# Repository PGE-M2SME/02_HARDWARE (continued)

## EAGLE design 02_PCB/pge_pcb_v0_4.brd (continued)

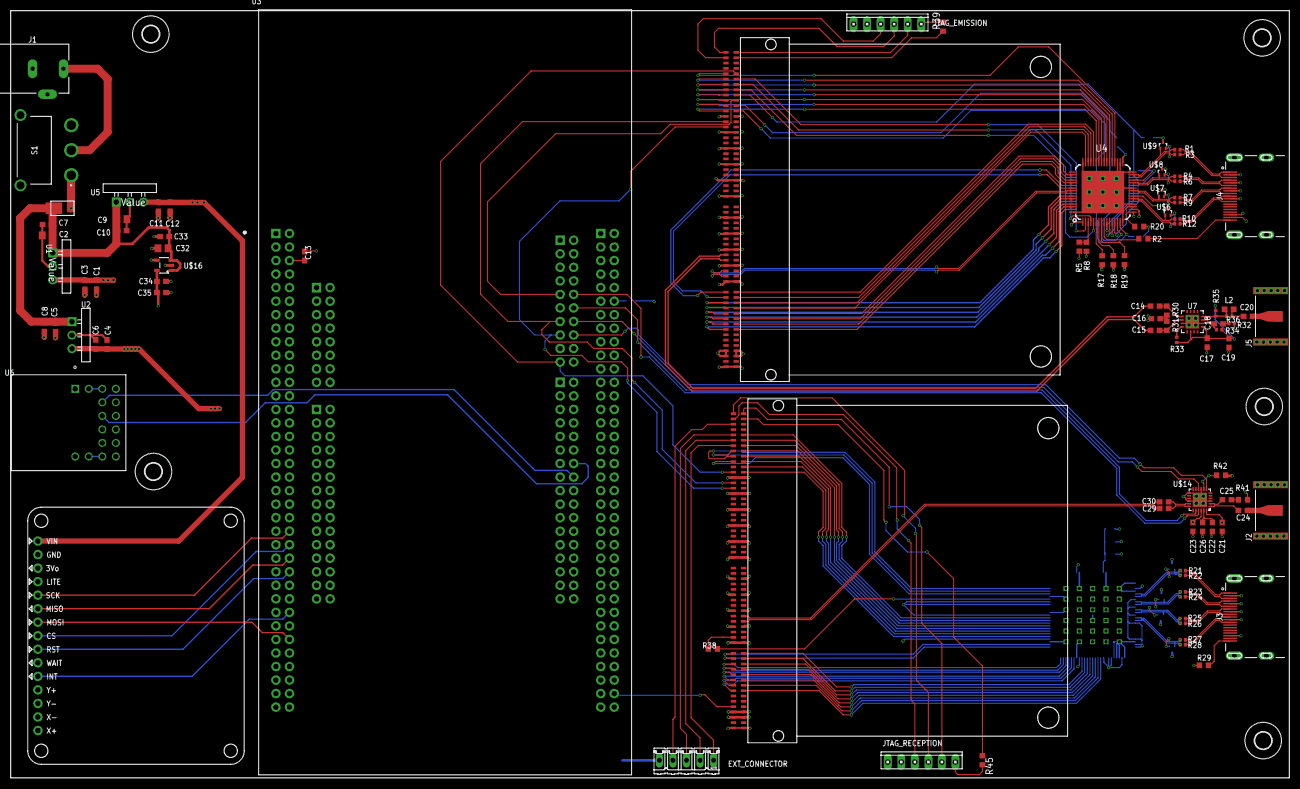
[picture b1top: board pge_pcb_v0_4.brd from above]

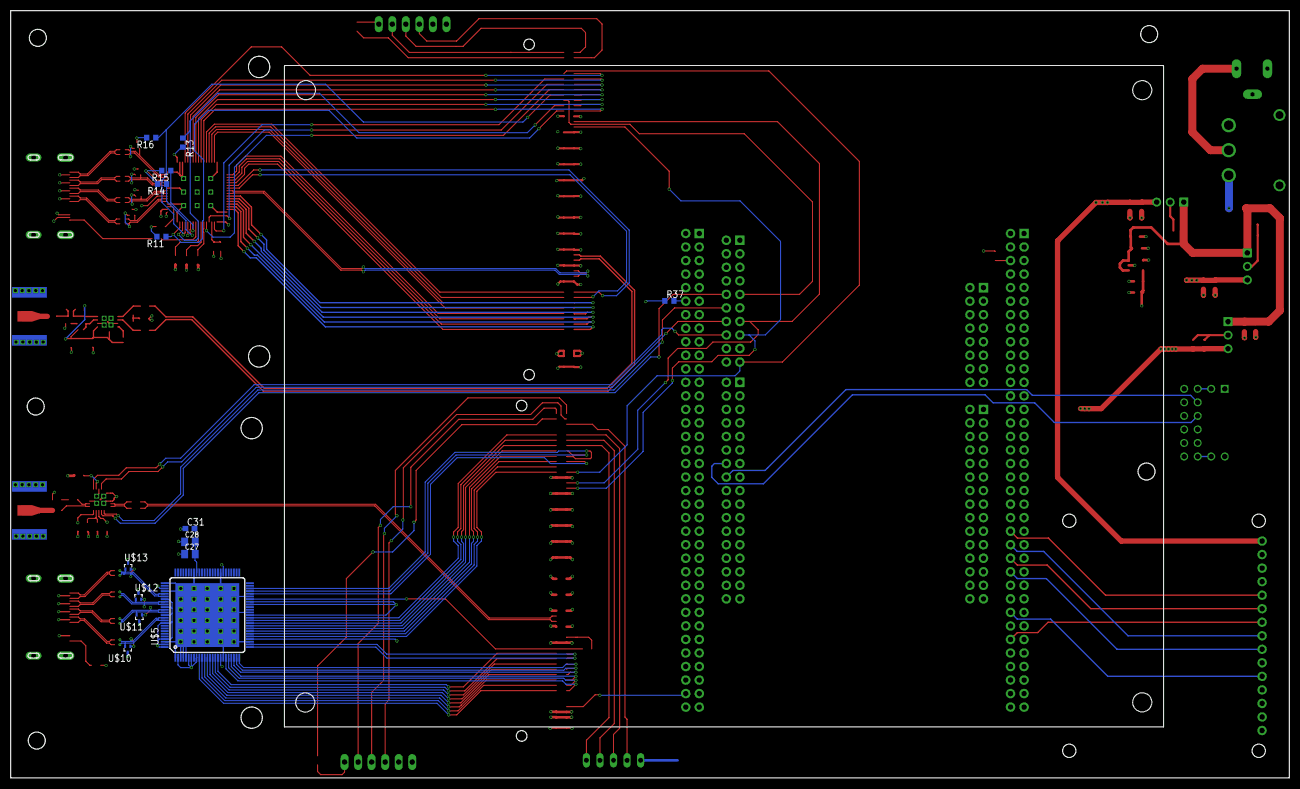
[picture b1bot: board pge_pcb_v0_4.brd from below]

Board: 6 copper layers, 240.0 x 144.0 mm, 115 parts (15 on the bottom side), 167 nets.

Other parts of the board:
H1, H2, H3, H7: MOUNT-HOLE3.2; 3,2

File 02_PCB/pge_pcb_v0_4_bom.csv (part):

"Qty";"Value";"Device";"Package";"Parts";"Description";"AMBIENT_TEMPERATURE_RANGE_HIGH";"AMBIENT_TEMPERATURE_RANGE_LOW";"ARROW_PART_NUMBER";"ARROW_PRICE-STOCK";"AUTOMOTIVE";"AVAILABILITY";"CENTROID_NOT_SPECIFIED";"DATASHEET";"DATASHEET-URL";"DESCRIPTION";"DEVICE_CLASS_L1";"DEVICE_CLASS_L2";"DEVICE_CLASS_L3";"DIGIKEY_DESCRIPTION";"DIGIKEY_PART_NUMBER";"FOOTPRINT_PARAMETERS_1";"FOOTPRINT_PARAMETERS_2";"FOOTPRINT_PARAMETERS_3";"FOOTPRINT_VARIANT_NAME_0";"FOOTPRINT_VARIANT_NAME_1";"FOOTPRINT_VARIANT_NAME_2";"FOOTPRINT_VARIANT_NAME_3";"GERDER";"HEIGHT";"INTERFACE";"IPC_LAND_PATTERN_NAME";"IR";"LEAD_FREE";"MANUFACTURER";"MANUFACTURER_NAME";"MANUFACTURER_PART_NUMBER";"MAXIMUM_PACKAGE_HEIGHT";"MAX_JUNCTION_TEMP";"MAX_SUPPLY_VOLTAGE";"MF";"MFG_PACKAGE_IDENT";"MFG_PACKAGE_IDENT_COMPONENT_ID";"MFG_PACKAGE_IDENT_DATE";"MFG_PACKAGE_IDENT_REV";"MIN_SUPPLY_VOLTAGE";"MOUNT";"MOUSER_DESCRIPTION";"MOUSER_PART_NUMBER";"MOUSER_PRICE-STOCK";"MP";"MPN";"NOMINAL_SUPPLY_CURRENT";"OC_FARNELL";"OC_NEWARK";"PACKAGE";"PART-NUMBER";"PARTNUMBER";"PARTREV";"PINS";"POPULARITY";"PREFIX";"PRICE";"PURCHASE-URL";"RATED-CURRENT";"REFDES";"ROHS";"SPICEPREFIX";"STANDARD";"TEMPERATURE_RANGE_HIGH";"TEMPERATURE_RANGE_LOW";"TYPE";"VALUE";"VERIFICATION_VERSION";"WORKING-VOLTAGE";
"2";"";"685119134923";"685119134923";"J3, J4";"WR-COM HDMI SMT Horizontal";"";"";"";"";"";"";"";"";"https://www.we-online.com/catalog/datasheet/685119134923.pdf";"";"";"";"";"";"";"";"";"";"";"";"";"";"Receptacle";"";"";"";"";"";"";"";"";"";"";"";"";"";"";"";"";"";"SMT";"";"";"";"";"";"";"";"";"";"685119134923";"";"";" 19 ";"";"";"";"";"0.5A";"";"";"";"";"";"";"Horizontal";"";"";"40VDC";
"1";"";"694106301002";"694106301002";"J1";"WR-DC DC Power Jack Right Angled (6.4)";"";"";"";"";"";"";"";"";"https://katalog.we-online.com/em/datasheet/694106301002.pdf";"";"";"";"";"";"";"";"";"";"";"";"";"";"";"";"";"";"5A";"";"";"";"";"";"";"";"";"";"";"";"";"";"THT";"";"";"";"";"";"";"";"";"";" 694106301002 ";"";"";"";"";"";"";"";"";"";"";"";"";"";"";"Right Angled";"";"";"30V(AC)";
"1";"";"M05";"05P";"EXT_CONNECTOR";"AMP QUICK CONNECTOR";"";"";"";"";"";"";"";"";"";"";"";"";"";"";"";"";"";"";"";"";"";"";"";"";"";"";"";"";"";"";"";"";"";"";"";"";"";"";"";"";"";"";"";"";"";"";"";"unknown";"unknown";"";"";"";"";"";"16";"";"";"";"";"";"";"";"";"";"";"";"";"";"";
"2";"";"MTA06-100";"10X06MTA";"JTAG_EMISSION, JTAG_RECEPTION";"AMP connector";"";"";"";"";"";"";"";"";"";"";"";"";"";"";"";"";"";"";"";"";"";"";"";"";"";"";"";"";"";"";"";"";"";"";"";"";"";"";"";"";"";"";"";"";"";"";"";"";"";"";"";"";"";"";"0";"";"";"";"";"";"";"";"";"";"";"";"";"";"";
"3";"0R";"R-EU_R0603";"R0603";"R17, R18, R19";"RESISTOR, European symbol";"";"";"";"";"";"";"";"";"";"";"";"";"";"";"";"";"";"";"";"";"";"";"";"";"";"";"";"";"";"";"";"";"";"";"";"";"";"";"";"";"";"";"";"";"";"";"";"";"";"";"";"";"";"";"70";"";"";"";"";"";"";"R";"";"";"";"";"";"";"";
"1";"1.5k";"R-EU_R0603";"R0603";"R37";"RESISTOR, European symbol";"";"";"";"";"";"";"";"";"";"";"";"";"";"";"";"";"";"";"";"";"";"";"";"";"";"";"";"";"";"";"";"";"";"";"";"";"";"";"";"";"";"";"";"";"";"";"";"";"";"";"";"";"";"";"70";"";"";"";"";"";"";"R";"";"";"";"";"";"";"";
"16";"100nF";"C-EUC0603";"C0603";"C1, C4, C7, C8, C10, C11, C13, C16, C17, C19, C21, C22, C23, C31, C33, C35";"CAPACITOR, European symbol";"";"";"";"";"";"";"";"";"";"";"";"";"";"";"";"";"";"";"";"";"";"";"";"";"";"";"";"";"";"";"";"";"";"";"";"";"";"";"";"";"";"";"";"";"";"";"";"";"";"";"";"";"";"";"73";"";"";"";"";"";"";"C";"";"";"";"";"";"";"";
"5";"10uF";"C-EUC0603";"C0603";"C3, C5, C6, C12, C34";"CAPACITOR, European symbol";"";"";"";"";"";"";"";"";"";"";"";"";"";"";"";"";"";"";"";"";"";"";"";"";"";"";"";"";"";"";"";"";"";"";"";"";"";"";"";"";"";"";"";"";"";"";"";"";"";"";"";"";"";"";"73";"";"";"";"";"";"";"C";"";"";"";"";"";"";"";
"3";"10uF";"C-EUC0805";"C0805";"C2, C9, C32";"CAPACITOR, European symbol";"";"";"";"";"";"";"";"";"";"";"";"";"";"";"";"";"";"";"";"";"";"";"";"";"";"";"";"";"";"";"";"";"";"";"";"";"";"";"";"";"";"";"";"";"";"";"";"";"";"";"";"";"";"";"88";"";"";"";"";"";"";"C";"";"";"";"";"";"";"";
"3";"1k";"R-EU_R0603";"R0603";"R2, R29, R42";"RESISTOR, European symbol";"";"";"";"";"";"";"";"";"";"";"";"";"";"";"";"";"";"";"";"";"";"";"";"";"";"";"";"";"";"";"";"";"";"";"";"";"";"";"";"";"";"";"";"";"";"";"";"";"";"";"";"";"";"";"70";"";"";"";"";"";"";"R";"";"";"";"";"";"";"";
"3";"1uF";"C-EUC0603";"C0603";"C14, C15, C26";"CAPACITOR, European symbol";"";"";"";"";"";"";"";"";"";"";"";"";"";"";"";"";"";"";"";"";"";"";"";"";"";"";"";"";"";"";"";"";"";"";"";"";"";"";"";"";"";"";"";"";"";"";"";"";"";"";"";"";"";"";"73";"";"";"";"";"";"";"C";"";"";"";"";"";"";"";
"1";"2.43K";"R-EU_R0603";"R0603";"R5";"RESISTOR, European symbol";"";"";"";"";"";"";"";"";"";"";"";"";"";"";"";"";"";"";"";"";"";"";"";"";"";"";"";"";"";"";"";"";"";"";"";"";"";"";"";"";"";"";"";"";"";"";"";"";"";"";"";"";"";"";"70";"";"";"";"";"";"";"R";"";"";"";"";"";"";"";
"1";"22R";"R-EU_R0603";"R0603";"R38";"RESISTOR, European symbol";"";"";"";"";"";"";"";"";"";"";"";"";"";"";"";"";"";"";"";"";"";"";"";"";"";"";"";"";"";"";"";"";"";"";"";"";"";"";"";"";"";"";"";"";"";"";"";"";"";"";"";"";"";"";"70";"";"";"";"";"";"";"R";"";"";"";"";"";"";"";
"2";"22uF";"C-EUC0805K";"C0805K";"C27, C28";"CAPACITOR, European symbol";"";"";"";"";"";"";"";"";"";"";"";"";"";"";"";"";"";"";"";"";"";"";"";"";"";"";"";"";"";"";"";"";"";"";"";"";"";"";"";"";"";"";"";"";"";"";"";"";"";"";"";"";"";"";"52";"";"";"";"";"";"";"C";"";"";"";"";"";"";"";
"16";"28R";"R-EU_R0402";"R0402";"R1, R3, R4, R6, R7, R9, R10, R12, R21, R22, R23, R24, R25, R26, R27, R28";"RESISTOR, European symbol";"";"";"";"";"";"";"";"";"";"";"";"";"";"";"";"";"";"";"";"";"";"";"";"";"";"";"";"";"";"";"";"";"";"";"";"";"";"";"";"";"";"";"";"";"";"";"";"";"";"";"";"";"";"";"0";"";"";"";"";"";"";"R";"";"";"";"";"";"";"";
"6";"4.7uF";"C-EUC0603";"C0603";"C18, C20, C24, C25, C29, C30";"CAPACITOR, European symbol";"";"";"";"";"";"";"";"";"";"";"";"";"";"";"";"";"";"";"";"";"";"";"";"";"";"";"";"";"";"";"";"";"";"";"";"";"";"";"";"";"";"";"";"";"";"";"";"";"";"";"";"";"";"";"73";"";"";"";"";"";"";"C";"";"";"";"";"";"";"";
"1";"499 R";"R-EU_R0603";"R0603";"R20";"RESISTOR, European symbol";"";"";"";"";"";"";"";"";"";"";"";"";"";"";"";"";"";"";"";"";"";"";"";"";"";"";"";"";"";"";"";"";"";"";"";"";"";"";"";"";"";"";"";"";"";"";"";"";"";"";"";"";"";"";"70";"";"";"";"";"";"";"R";"";"";"";"";"";"";"";
"2";"50R";"R-EU_R0603";"R0603";"R30, R31";"RESISTOR, European symbol";"";"";"";"";"";"";"";"";"";"";"";"";"";"";"";"";"";"";"";"";"";"";"";"";"";"";"";"";"";"";"";"";"";"";"";"";"";"";"";"";"";"";"";"";"";"";"";"";"";"";"";"";"";"";"70";"";"";"";"";"";"";"R";"";"";"";"";"";"";"";
"5";"5k";"R-EU_R0603";"R0603";"R11, R13, R14, R15, R16";"RESISTOR, European symbol";"";"";"";"";"";"";"";"";"";"";"";"";"";"";"";"";"";"";"";"";"";"";"";"";"";"";"";"";"";"";"";"";"";"";"";"";"";"";"";"";"";"";"";"";"";"";"";"";"";"";"";"";"";"";"70";"";"";"";"";"";"";"R";"";"";"";"";"";"";"";
"1";"6.8nH";"L0603";"L0603";"L2";"";"";"";"";"";"";"";"";"";"";"";"";"";"";"";"";"";"";"";"";"";"";"";"";"";"";"";"";"";"";"";"";"";"";"";"";"";"";"";"";"";"";"";"";"";"";"";"";"";"";"";"";"";"";"";"";"";"";"";"";"";"";"";"";"";"";"";"";"";"";
"1";"750R";"R-EU_R0402";"R0402";"R33";"RESISTOR, European symbol";"";"";"";"";"";"";"";"";"";"";"";"";"";"";"";"";"";"";"";"";"";"";"";"";"";"";"";"";"";"";"";"";"";"";"";"";"";"";"";"";"";"";"";"";"";"";"";"";"";"";"";"";"";"";"0";"";"";"";"";"";"";"R";"";"";"";"";"";"";"";
"4";"75R";"R-EU_R0402";"R0402";"R32, R34, R35, R36";"RESISTOR, European symbol";"";"";"";"";"";"";"";"";"";"";"";"";"";"";"";"";"";"";"";"";"";"";"";"";"";"";"";"";"";"";"";"";"";"";"";"";"";"";"";"";"";"";"";"";"";"";"";"";"";"";"";"";"";"";"0";"";"";"";"";"";"";"R";"";"";"";"";"";"";"";
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
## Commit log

2020-11-01 add statut cw44
2020-11-01 ADD 3D files
2020-11-04 upload folder equipe management (HW)
2021-04-10 pcb schematic & board v0.4
2021-04-10 folder organisation: move to 01_composants
